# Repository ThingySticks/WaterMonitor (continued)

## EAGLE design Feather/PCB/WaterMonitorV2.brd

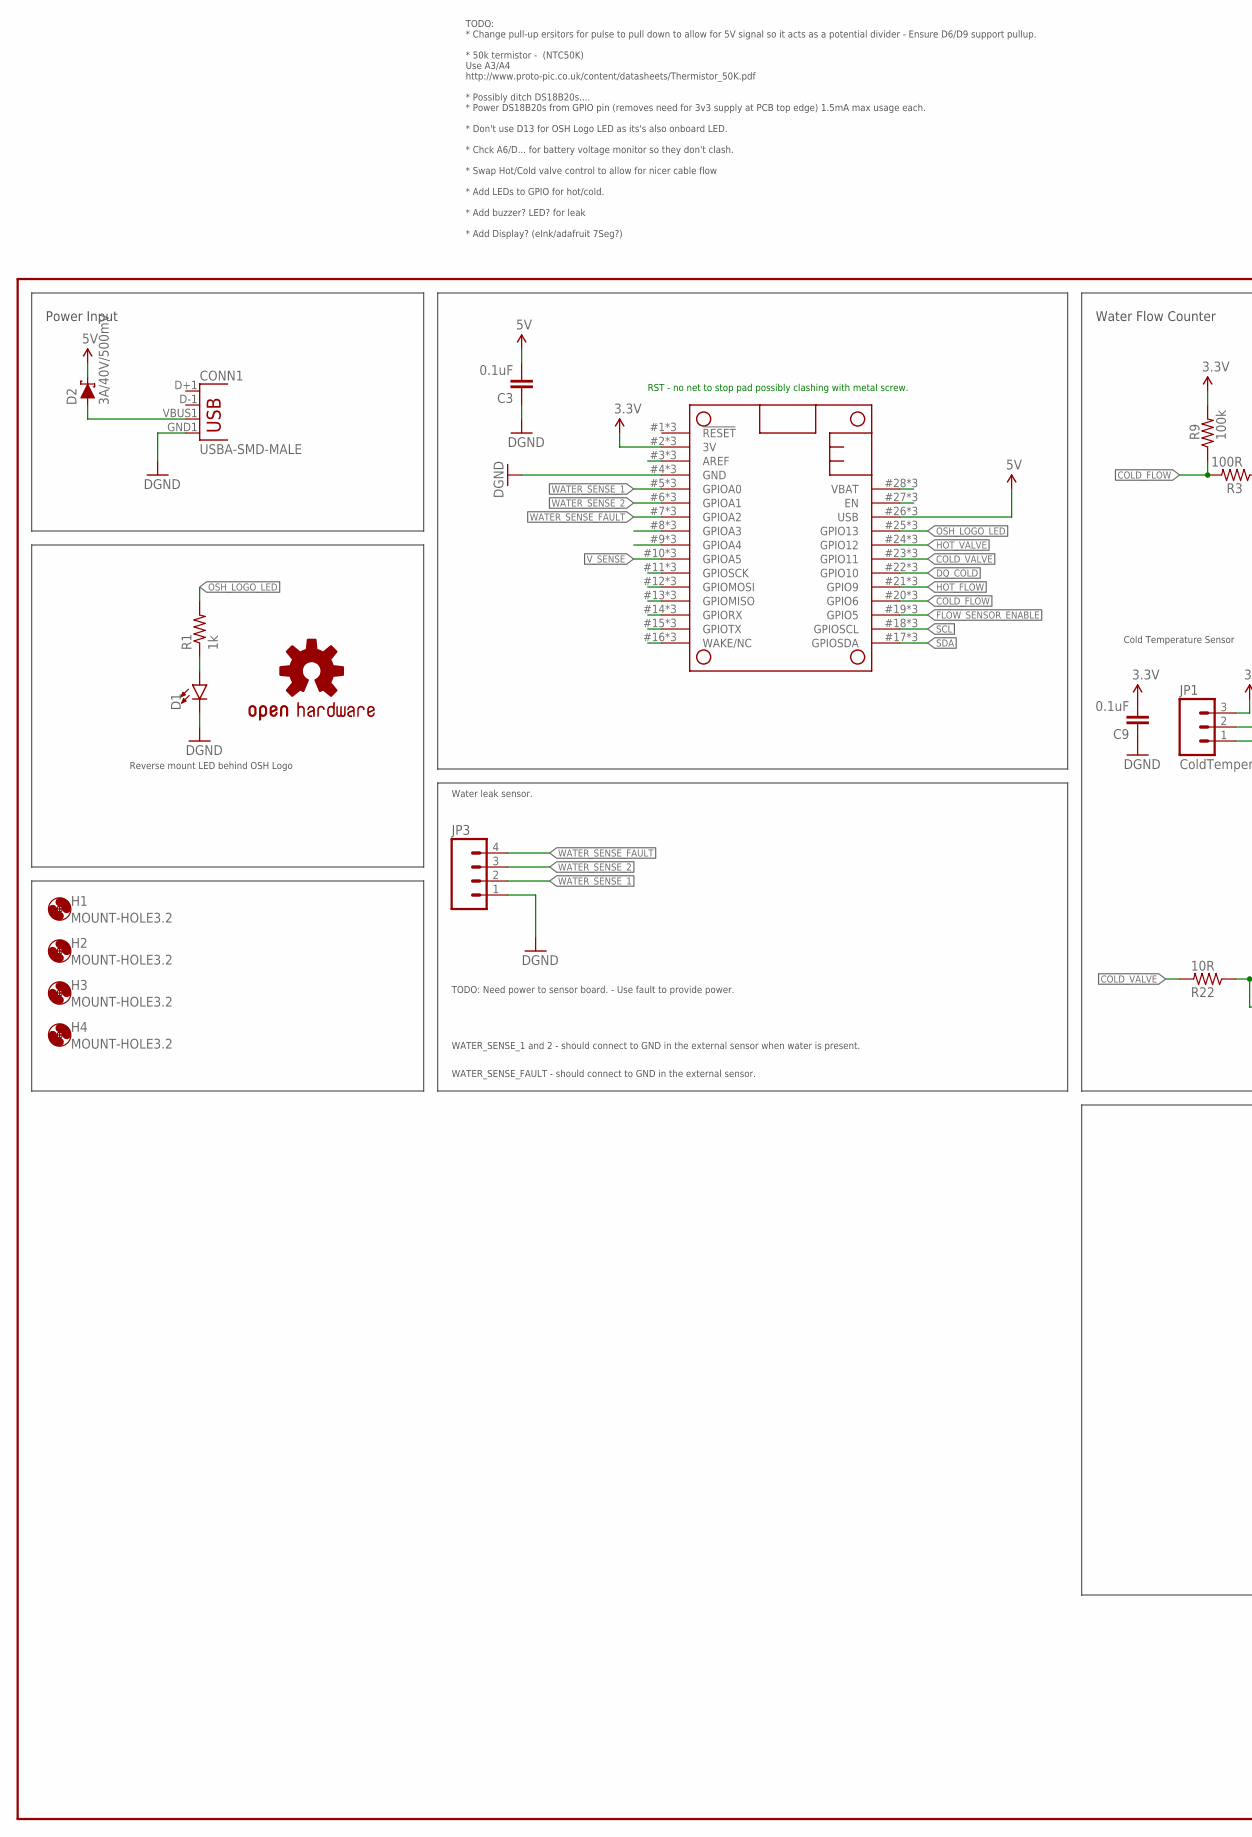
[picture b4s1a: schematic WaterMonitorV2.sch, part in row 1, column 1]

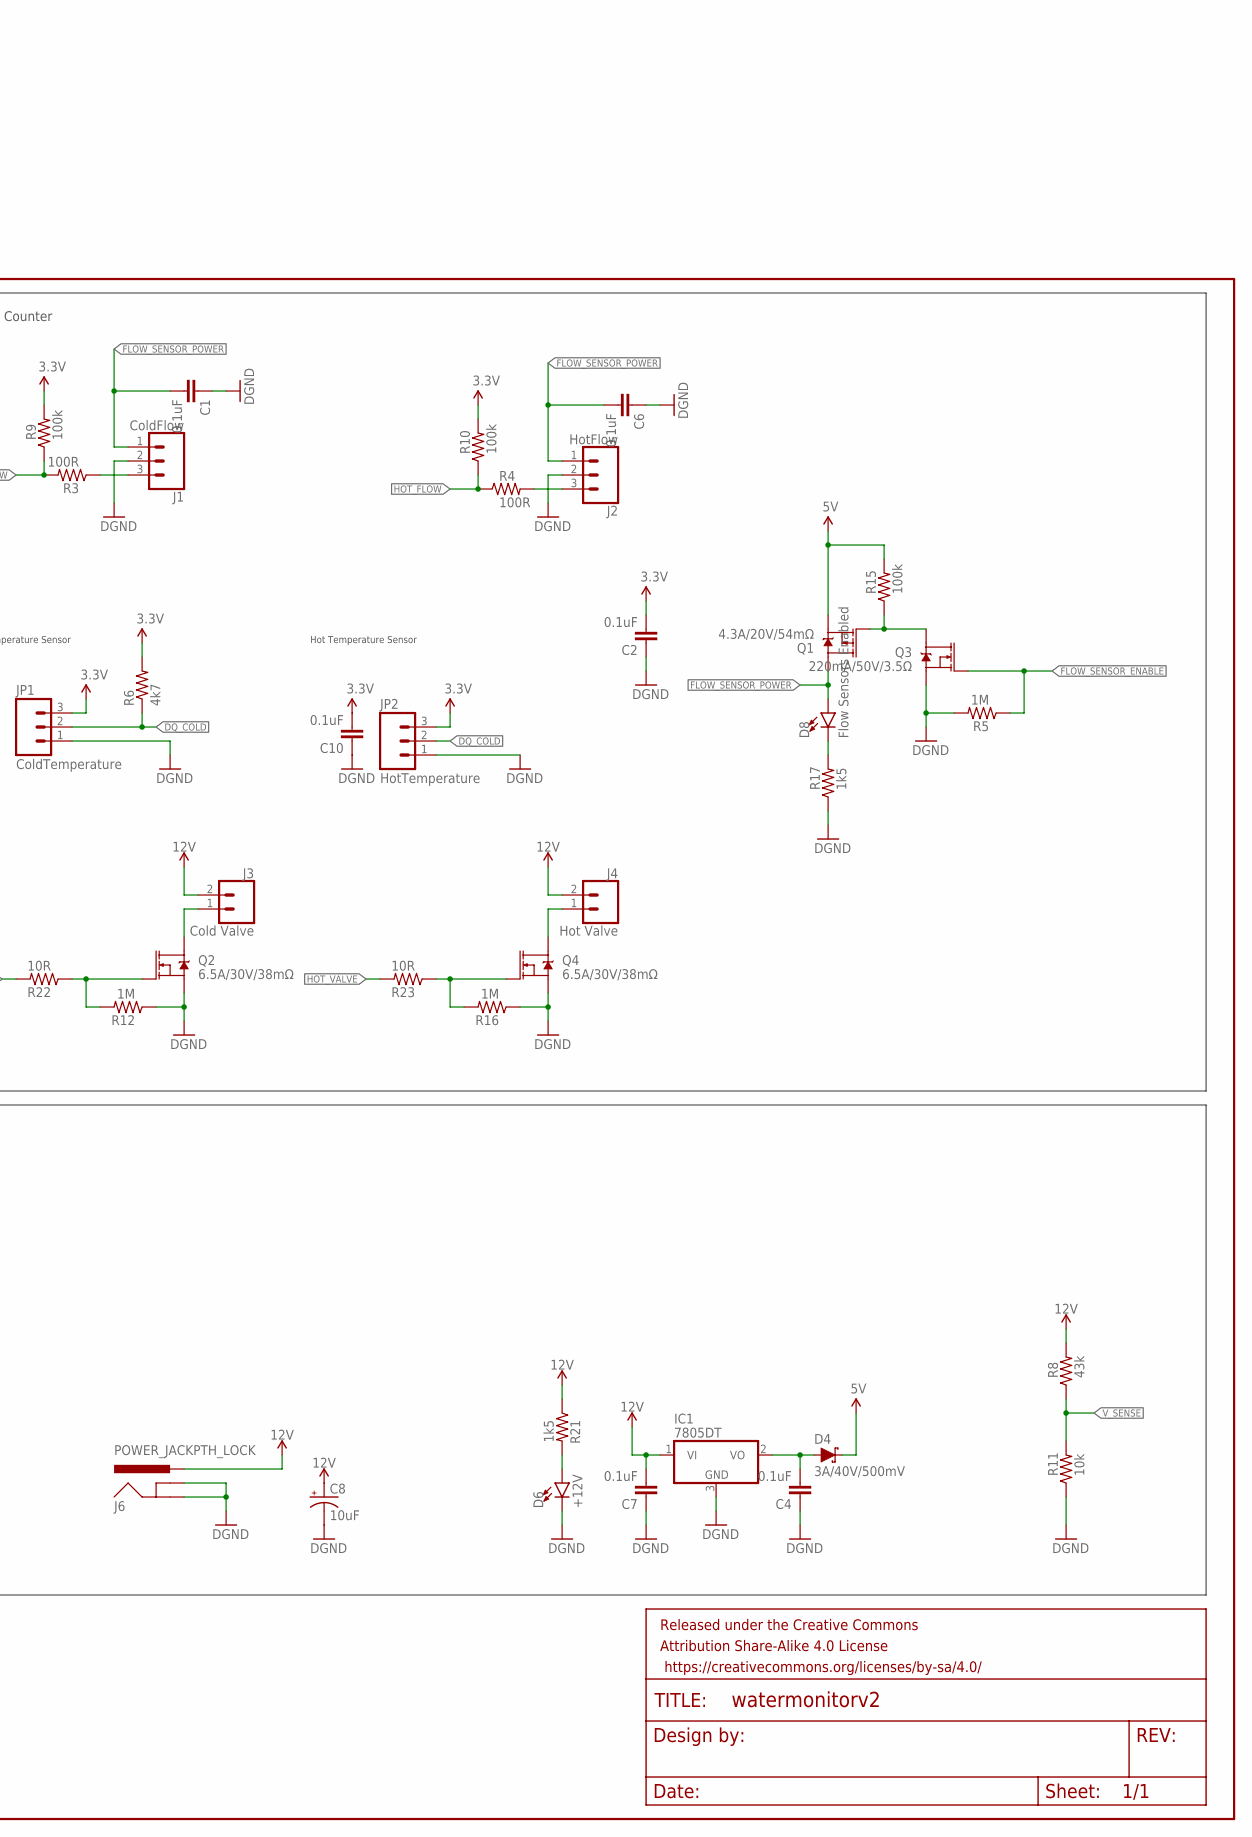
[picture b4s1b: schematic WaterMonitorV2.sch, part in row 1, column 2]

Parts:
C1, C2, C3, C4, C6, C7, C9, C10: 0.1uF; 0805
C8: 10uF; EIA3216
CONN1: USBA-SMD-MALE; USB-A-SMT-MALE
D1: LED1206-BOTTOM; LED-1206-BOTTOM
D2, D4: 3A/40V/500mV; SMA-DIODE
D6: +12V; LED-1206
D8: Flow Sensors Enabled; LED-1206
FRAME2: FRAME-LEDGER; CREATIVE_COMMONS
H1, H2, H3, H4: MOUNT-HOLE3.2; 3,2
IC1: 7805DT; TO252
J1: ColdFlow; JST-HX-3-PTH-VERT
J2: HotFlow; JST-HX-3-PTH-VERT
J3: Cold Valve; SCREWTERMINAL-5MM-2
J4: Hot Valve; SCREWTERMINAL-5MM-2
J6: POWER_JACKPTH_LOCK; POWER_JACK_PTH_LOCK
JP1: ColdTemperature; MOLEX-1X3
JP2: HotTemperature; MOLEX-1X3
JP3: M04POLAR; MOLEX-1X4
LOGO1: OSHW-LOGOM; OSHW-LOGO-M
MS1: FEATHERWINGFEATHEWING_BREAKOUT; FEATHERWING_BREAKOUT
Q1: 4.3A/20V/54mΩ; SOT23-3
Q2, Q4: 6.5A/30V/38mΩ; SO08
Q3: 220mA/50V/3.5Ω; SOT23-3
R1: 1k; 1206
R3, R4: 100R; 0805
R5, R12, R16: 1M; 0805
R6: 4k7; 0805
R8: 43k; 0805
R9, R10, R15: 100k; 0805
R11: 10k; 0805
R17, R21: 1k5; 0805
R22, R23: 10R; 0805

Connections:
3.3V: C2.2, C9.2, C10.2, JP1.3, JP2.3, MS1.2 (3V), MS1.#2 (3V), MS1.@2 (3V), R6.2, R9.2, R10.2
5V: C3.2, D2.C, D4.C, MS1.26 (USB), MS1.#26 (USB), MS1.@26 (USB), Q1.2 (S), R15.2
12V: C7.2, C8.+, IC1.1 (VI), J3.2, J4.2, J6.PWR, R8.2, R21.1
COLD_FLOW: MS1.20 (GPIO6), MS1.#20 (GPIO6), MS1.@20 (GPIO6), R3.2, R9.1
COLD_VALVE: MS1.23 (GPIO11), MS1.#23 (GPIO11), MS1.@23 (GPIO11), R22.2
DQ_COLD: JP1.2, JP2.2, MS1.22 (GPIO10), MS1.#22 (GPIO10), MS1.@22 (GPIO10), R6.1
FLOW_SENSOR_ENABLE: MS1.19 (GPIO5), MS1.#19 (GPIO5), MS1.@19 (GPIO5), Q3.1 (G), R5.1
FLOW_SENSOR_POWER: C1.2, C6.2, D8.A, J1.1, J2.1, Q1.3 (D)
GND: C1.1, C2.1, C3.1, C4.1, C6.1, C7.1, C8.-, C9.1, C10.1, CONN1.GND1 (GND), D1.C, D6.C, IC1.3 (GND), J1.2, J2.2, J6.GND, J6.GNDBREAK, JP1.1, JP2.1, JP3.1, MS1.4 (GND), MS1.#4 (GND), MS1.@4 (GND), Q2.1 (S), Q2.2 (S), Q2.3 (S), Q3.2 (S), Q4.1 (S), Q4.2 (S), Q4.3 (S), R5.2, R11.1, R12.1, R16.1, R17.1
HOT_FLOW: MS1.21 (GPIO9), MS1.#21 (GPIO9), MS1.@21 (GPIO9), R4.1, R10.1
HOT_VALVE: MS1.24 (GPIO12), MS1.#24 (GPIO12), MS1.@24 (GPIO12), R23.2
unnamed: CONN1.VBUS1 (VBUS), D2.A
unnamed: J1.3, R3.1
unnamed: J2.3, R4.2
unnamed: D8.C, R17.2
unnamed: MS1.8 (GPIOA3), MS1.#8 (GPIOA3), MS1.@8 (GPIOA3)
unnamed: D6.A, R21.2
unnamed: MS1.27 (EN), MS1.#27 (EN), MS1.@27 (EN)
unnamed: MS1.9 (GPIOA4), MS1.#9 (GPIOA4), MS1.@9 (GPIOA4)
unnamed: Q1.1 (G), Q3.3 (D), R15.1
unnamed: MS1.3 (AREF), MS1.#3 (AREF), MS1.@3 (AREF)
unnamed: D1.A, R1.1
unnamed: Q2.4 (G), R12.2, R22.1
unnamed: Q4.4 (G), R16.2, R23.1
unnamed: J3.1, Q2.5 (D), Q2.6 (D), Q2.7 (D), Q2.8 (D)
unnamed: J4.1, Q4.5 (D), Q4.6 (D), Q4.7 (D), Q4.8 (D)
unnamed: MS1.11 (GPIOSCK), MS1.#11 (GPIOSCK), MS1.@11 (GPIOSCK)
unnamed: MS1.12 (GPIOMOSI), MS1.#12 (GPIOMOSI), MS1.@12 (GPIOMOSI)
unnamed: MS1.13 (GPIOMISO), MS1.#13 (GPIOMISO), MS1.@13 (GPIOMISO)
unnamed: MS1.14 (GPIORX), MS1.#14 (GPIORX), MS1.@14 (GPIORX)
unnamed: MS1.15 (GPIOTX), MS1.#15 (GPIOTX), MS1.@15 (GPIOTX)
unnamed: MS1.16 (WAKE/NC), MS1.#16 (WAKE/NC), MS1.@16 (WAKE/NC)
unnamed: C4.2, D4.A, IC1.2 (VO)
OSH_LOGO_LED: MS1.25 (GPIO13), MS1.#25 (GPIO13), MS1.@25 (GPIO13), R1.2
SCL: MS1.18 (GPIOSCL), MS1.#18 (GPIOSCL), MS1.@!8 (GPIOSCL)
SDA: MS1.17 (GPIOSDA), MS1.#17 (GPIOSDA), MS1.@17 (GPIOSDA)
VBAT: MS1.28 (VBAT), MS1.#28 (VBAT), MS1.@28 (VBAT)
V_SENSE: MS1.10 (GPIOA5), MS1.#10 (GPIOA5), MS1.@10 (GPIOA5), R8.1, R11.2
WATER_SENSE_1: JP3.2, MS1.5 (GPIOA0), MS1.#5 (GPIOA0), MS1.@5 (GPIOA0)
WATER_SENSE_2: JP3.3, MS1.6 (GPIOA1), MS1.#6 (GPIOA1), MS1.@6 (GPIOA1)
WATER_SENSE_FAULT: JP3.4, MS1.7 (GPIOA2), MS1.#7 (GPIOA2), MS1.@7 (GPIOA2)

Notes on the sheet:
Water Flow Counter
Power Input
Hot Temperature Sensor
Reverse mount LED behind OSH Logo
Cold Temperature Sensor
RST - no net to stop pad possibly clashing with metal screw.
Water leak sensor.
WATER_SENSE_FAULT - should connect to GND in the external sensor.
WATER_SENSE_1 and 2 - should connect to GND in the external sensor when water is present.
TODO: * Change pull-up ersitors for pulse to pull down to allow for 5V signal so it acts as a potential divider - Ensure D6/D9 support pullup. * 50k termistor - (NTC50K) Use A3/A4 http://www.proto-pic.co.uk/content/datasheets/Thermistor_50K.pdf * Possibly ditch DS18B20s.... * Power DS18B20s from GP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
TODO: Need power to sensor board. - Use fault to provide power.

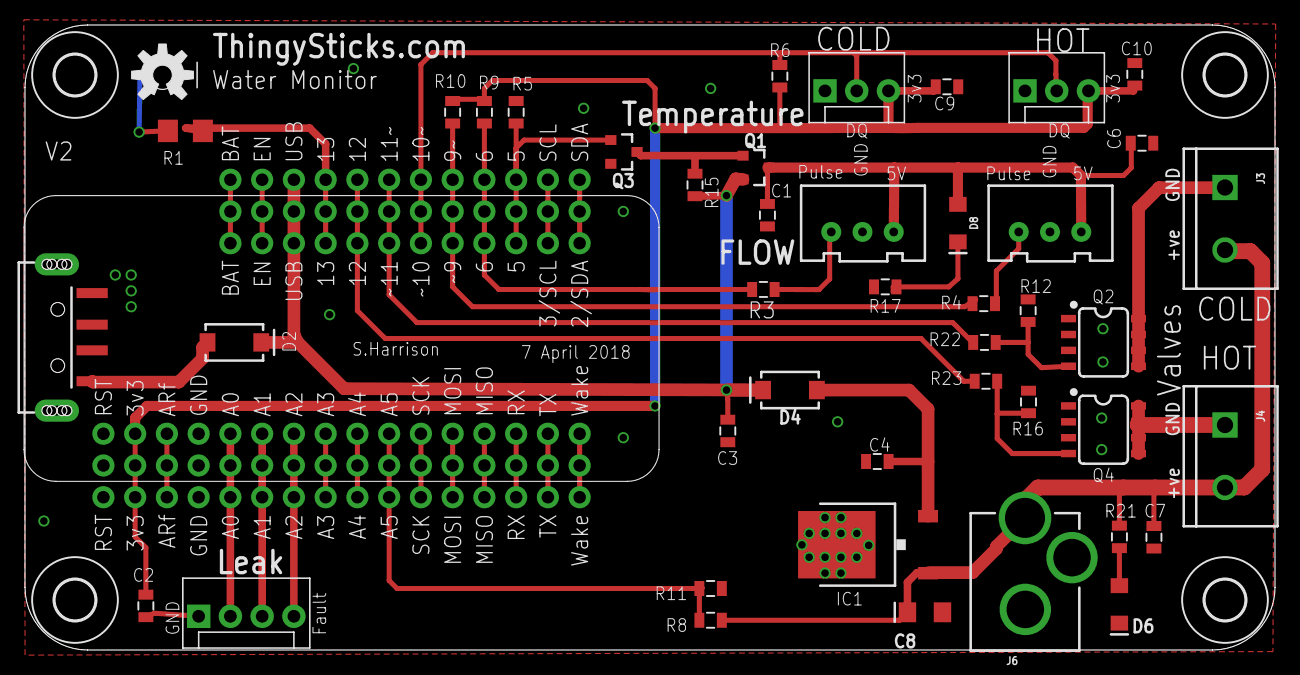
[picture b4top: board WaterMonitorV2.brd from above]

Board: 2 copper layers, 100.0 x 50.0 mm, 51 parts (1 on the bottom side), 41 nets.

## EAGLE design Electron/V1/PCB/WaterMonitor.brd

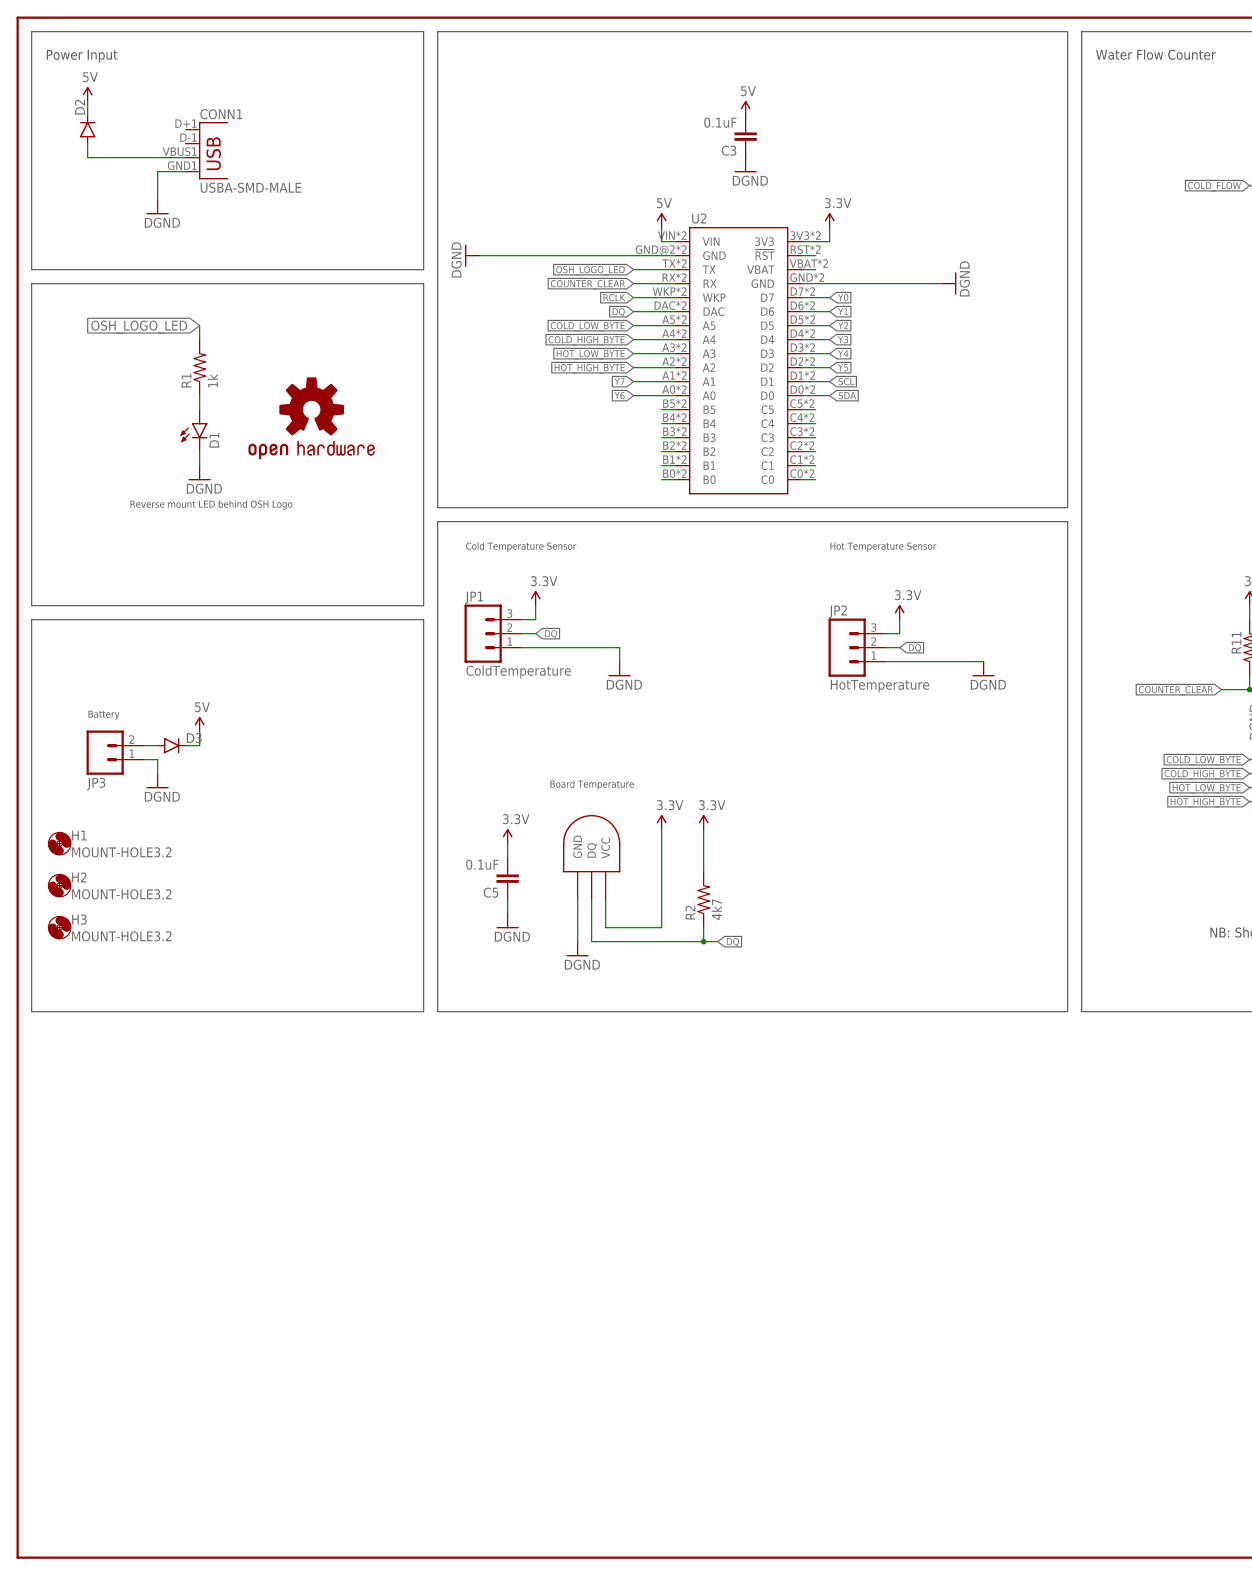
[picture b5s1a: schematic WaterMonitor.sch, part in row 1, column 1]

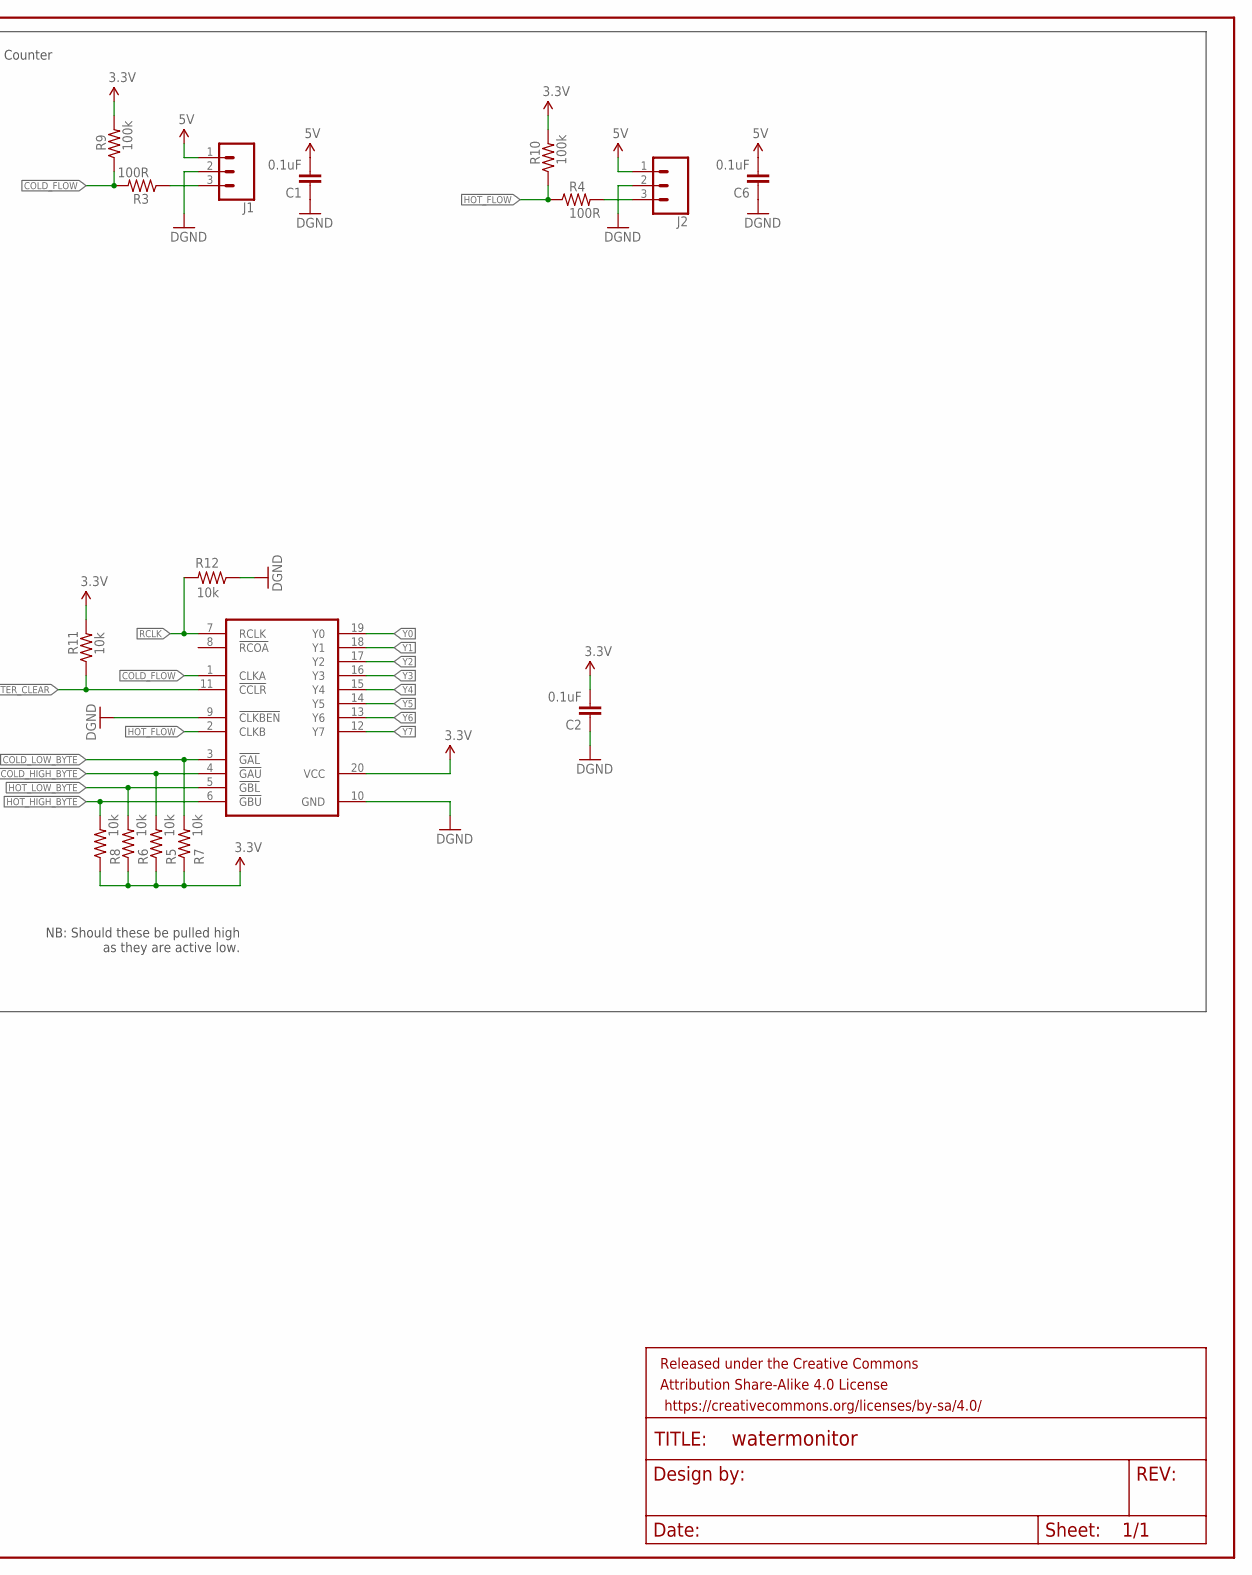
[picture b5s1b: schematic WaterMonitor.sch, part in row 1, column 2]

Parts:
C1, C2, C3, C5, C6: 0.1uF; 0805
CONN1: USBA-SMD-MALE; USB-A-SMT-MALE
D1: LED1206-BOTTOM; LED-1206-BOTTOM
D2, D3: DIODESMA; SMA-DIODE
FRAME2: FRAME-LEDGER; CREATIVE_COMMONS
H1, H2, H3: MOUNT-HOLE3.2; 3,2
J1, J2: CONN_03JST-HX-PTH-VERT; JST-HX-3-PTH-VERT
JP1: ColdTemperature; MOLEX-1X3
JP2: HotTemperature; MOLEX-1X3
JP3: M02-JST-2MM-SMT; JST-2-SMD
LOGO1: OSHW-LOGOM; OSHW-LOGO-M
R1: 1k; 1206
R2: 4k7; 0805
R3, R4: 100R; 0805
R5, R6, R7, R8, R11, R12: 10k; 0805
R9, R10: 100k; 0805
U1: SN74LV8154PW; TSSOP20
U2: ELECTRONDUALNAMED; ELECTRON_SIMPLE_SILK_NAMES_DUAL
U4: DS1820SOIC; DS18B20_SOIC

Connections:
3.3V: C2.2, C5.2, JP1.3, JP2.3, R2.2, R5.1, R6.1, R7.1, R8.1, R9.2, R10.2, R11.2, U1.20 (VCC), U2.3V3, U2.3V3_1 (3V3), U4.VCC
5V: C1.2, C3.2, C6.2, D2.C, D3.C, J1.1, J2.1, U2.VIN, U2.VIN_1B (VIN)
COLD_FLOW: R3.2, R9.1, U1.1 (CLKA)
COLD_HIGH_BYTE: R5.2, U1.4 (!GAU!), U2.A4, U2.A4_1 (A4)
COLD_LOW_BYTE: R7.2, U1.3 (!GAL!), U2.A5, U2.A5_1 (A5)
COUNTER_CLEAR: R11.1, U1.11 (!CCLR!), U2.RX, U2.RX_1 (RX)
DQ: JP1.2, JP2.2, R2.1, U2.DAC, U2.DAC_1 (DAC), U4.DQ
GND: C1.1, C2.1, C3.1, C5.1, C6.1, CONN1.GND1 (GND), D1.C, J1.2, J2.2, JP1.1, JP2.1, JP3.1 (2), R12.1, U1.9 (!CLKBEN!), U1.10 (GND), U2.GND, U2.GND@2 (GND), U2.GND_1 (GND), U2.GND_1B (GND), U4.GND
HOT_FLOW: R4.1, R10.1, U1.2 (CLKB)
HOT_HIGH_BYTE: R8.2, U1.6 (!GBU!), U2.A2, U2.A2_1 (A2)
HOT_LOW_BYTE: R6.2, U1.5 (!GBL!), U2.A3, U2.A3_1 (A3)
unnamed: CONN1.VBUS1 (VBUS), D2.A
unnamed: J1.3, R3.1
unnamed: J2.3, R4.2
unnamed: U2.VBAT, U2.VBATT_1 (VBAT)
unnamed: U2.RST (!RST), U2.RST_1 (!RST)
unnamed: D1.A, R1.1
unnamed: U2.C1, U2.C1_1 (C1)
unnamed: U2.C5, U2.C5_1 (C5)
unnamed: U2.C4, U2.C4_1 (C4)
unnamed: U2.C3, U2.C3_1 (C3)
unnamed: U2.C2, U2.C2_1 (C2)
unnamed: U2.C0, U2.C0_1 (C0)
unnamed: D3.A, JP3.2 (1)
unnamed: U2.B0, U2.B0_1 (B0)
unnamed: U2.B1, U2.B1_1 (B1)
unnamed: U2.B2, U2.B2_1 (B2)
unnamed: U2.B3, U2.B3_1 (B3)
unnamed: U2.B4, U2.B4_1 (B4)
unnamed: U2.B5, U2.B5_1 (B5)
OSH_LOGO_LED: R1.2, U2.TX, U2.TX_1 (TX)
RCLK: R12.2, U1.7 (RCLK), U2.WKP, U2.WKP_1 (WKP)
SCL: U2.D1, U2.D1_1 (D1)
SDA: U2.D0, U2.D0_1 (D0)
Y0: U1.19 (Y0), U2.D7, U2.D7_1 (D7)
Y1: U1.18 (Y1), U2.D6, U2.D6_1 (D6)
Y2: U1.17 (Y2), U2.D5, U2.D5_1 (D5)
Y3: U1.16 (Y3), U2.D4, U2.D4_1 (D4)
Y4: U1.15 (Y4), U2.D3, U2.D3_1 (D3)
Y5: U1.14 (Y5), U2.D2, U2.D2_1 (D2)
Y6: U1.13 (Y6), U2.A0, U2.A0_1 (A0)
Y7: U1.12 (Y7), U2.A1, U2.A1_1 (A1)

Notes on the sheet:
Water Flow Counter
Power Input
Hot Temperature Sensor
Board Temperature
Reverse mount LED behind OSH Logo
Battery
Cold Temperature Sensor
NB: Should these be pulled high as they are active low.

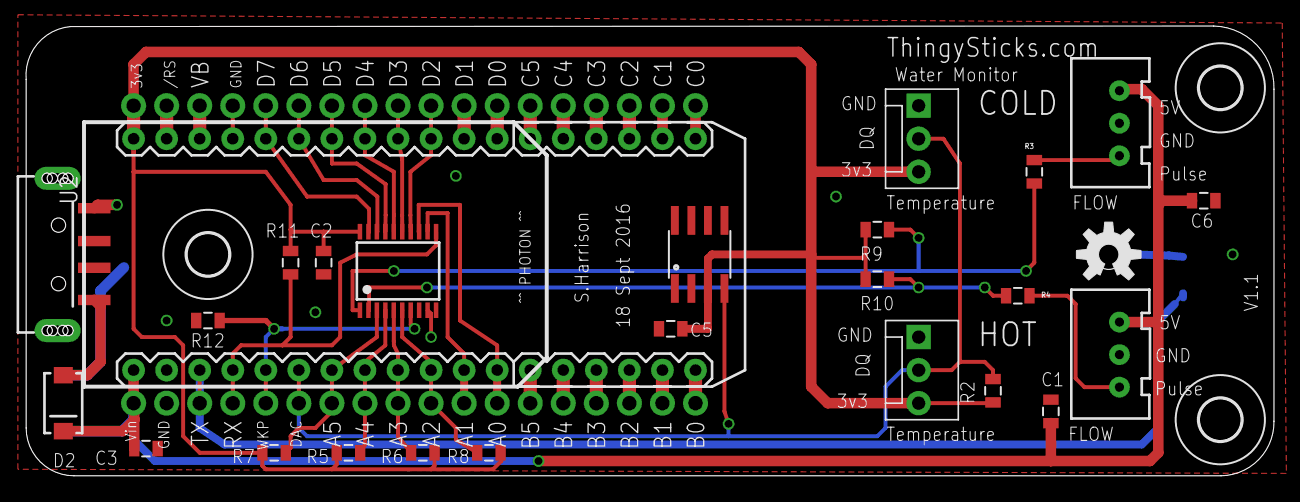
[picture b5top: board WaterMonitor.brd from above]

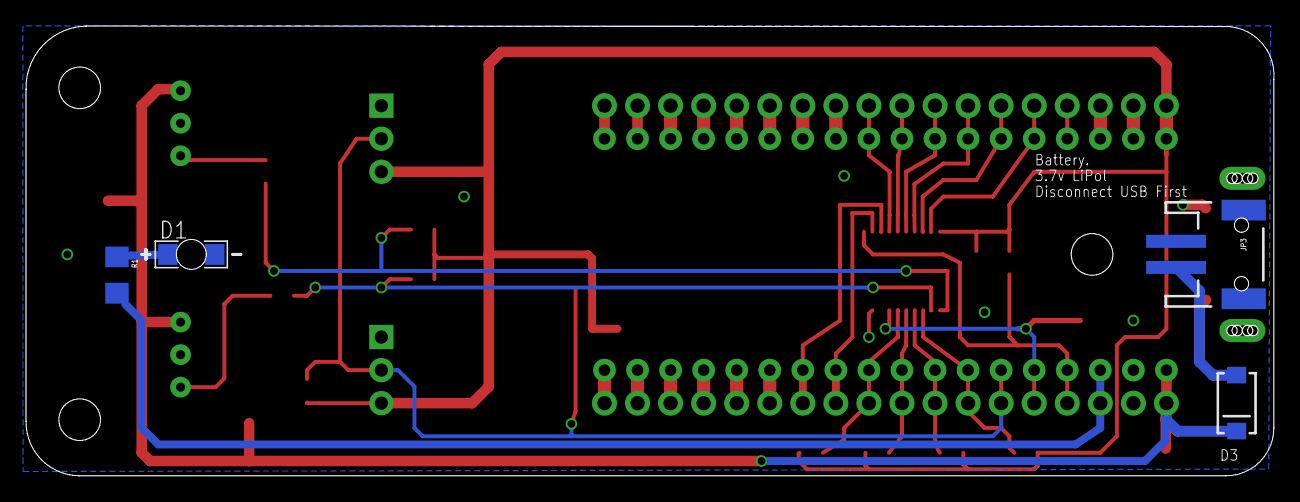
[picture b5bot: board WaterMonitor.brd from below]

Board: 2 copper layers, 95.9 x 34.6 mm, 34 parts (4 on the bottom side), 42 nets.

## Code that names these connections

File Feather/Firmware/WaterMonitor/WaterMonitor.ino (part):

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#define COLD_FLOW_PULSE_PIN 6
#define HOT_FLOW_PULSE_PIN 9
#define TEMPERATURE_DQ_PIN 10
#define COLD_VALVE_PIN 11
#define HOT_VALVE_PIN 12

#define EXTERNAL_VOLTAGE_SENSE_PIN A5 
#define LEAK_SENSE_FAULT_PIN A2
#define LEAK_SENSE_2_PIN A1
#define LEAK_SENSE_1_PIN A0

// Maximum number of sensors.
#define SENSOR_COUNT 2
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  pinMode(COLD_FLOW_PULSE_PIN, INPUT);
  pinMode(HOT_FLOW_PULSE_PIN, INPUT); 
  pinMode(TEMPERATURE_DQ_PIN, INPUT); 
  pinMode(COLD_VALVE_PIN, OUTPUT); 
  pinMode(HOT_VALVE_PIN, OUTPUT);

  pinMode(EXTERNAL_VOLTAGE_SENSE_PIN, INPUT); 
  pinMode(LEAK_SENSE_FAULT_PIN, INPUT); 
  pinMode(LEAK_SENSE_2_PIN, INPUT);
  pinMode(LEAK_SENSE_1_PIN, INPUT);

  // Enable the sensors
  setSensorPower(true);
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  // If no leak sensor is connected these will be all over the place.
  // fault pin might need to be modified to be power to the leak sensor.
  leakSenseFault = analogRead(LEAK_SENSE_FAULT_PIN);
  leakSense2 = analogRead(LEAK_SENSE_2_PIN);
  leakSense1 = analogRead(LEAK_SENSE_1_PIN);
}

// Compute the flow rate this interval.
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
// Set the Hot valve state (true = open, false = closed);
void setHotValve(bool valveOpen) {
  digitalWrite(HOT_VALVE_PIN, valveOpen); 
  hotValveEnabled = valveOpen;

}

// Set the Cold valve state (true = open, false = closed);
void setColdValve(bool valveOpen) {
  digitalWrite(COLD_VALVE_PIN, valveOpen);
  coldValveEnabled = valveOpen;
}

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
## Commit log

2016-09-18 V1 as sent to DirtyPCBs
2016-10-08 Minor tidy for part names etc.
    Added pdf's for V1 PCB.
2017-06-01 Tidy up
2018-07-20 Version 2.1 (as sent to DirtyPCBs).
    Added Grove I2C connector for display/sensors etc.
    Removed DS18B20 temperature sensors instead using 50k thermistors as these are available for some flow sensors and on their own for water temperature measurements.
    Added F2 to allow USB power to be supplied to the "valuve" FET switched outputs and also to allow 5V DC jack usage withtout the 7805.
    Added Hot/Cold valve LEDs.
    Stopped using D9 as this is also used for battery monitor where that is available.
    Added F1 fuse for USB power protection from the Feather board.
2018-07-20 Adding V2 PCB (feather).
2018-07-20 Basic initial version of the firmware for V2 to pulse count.
2018-07-20 V1.1 changes - not sure what. Not important - not using this version any more.
2018-07-20 Added images for V2.1
    Remove todo text from schematic.
    Changed water sense fault net to water sense power.
2018-07-21 Moved V2 PCBs from Electron to Feather as they are feather based.
2018-07-21 Added V5 - 5 port flow/temperature only.
    As sent to DirtyPCBs.
2018-07-22 Added Version 6.
    6 ports, with Group C (flow 5/6) configurable for temperature measurements.
    Modified to use RJ11's for flow connections to simplify installation.
    As sent to DirtyPCBs.
2019-02-11 Added V7 PCB design, to fit Camdenboss enclosure and use 2 port onboard JST connector and 2 port RJ11 external connections.
2019-02-11 Improvements to firmware for flow rate monitoring.
2019-02-11 Added missing junction
2019-04-04 Moved OSH LED, added values.
2019-04-04 V7.1 - added JST 2mm 2 pin connector for power on underside of board so the USB connection isn't required.
2019-04-04 First pass RJ11 to 3 pin flow sensor adaptors
